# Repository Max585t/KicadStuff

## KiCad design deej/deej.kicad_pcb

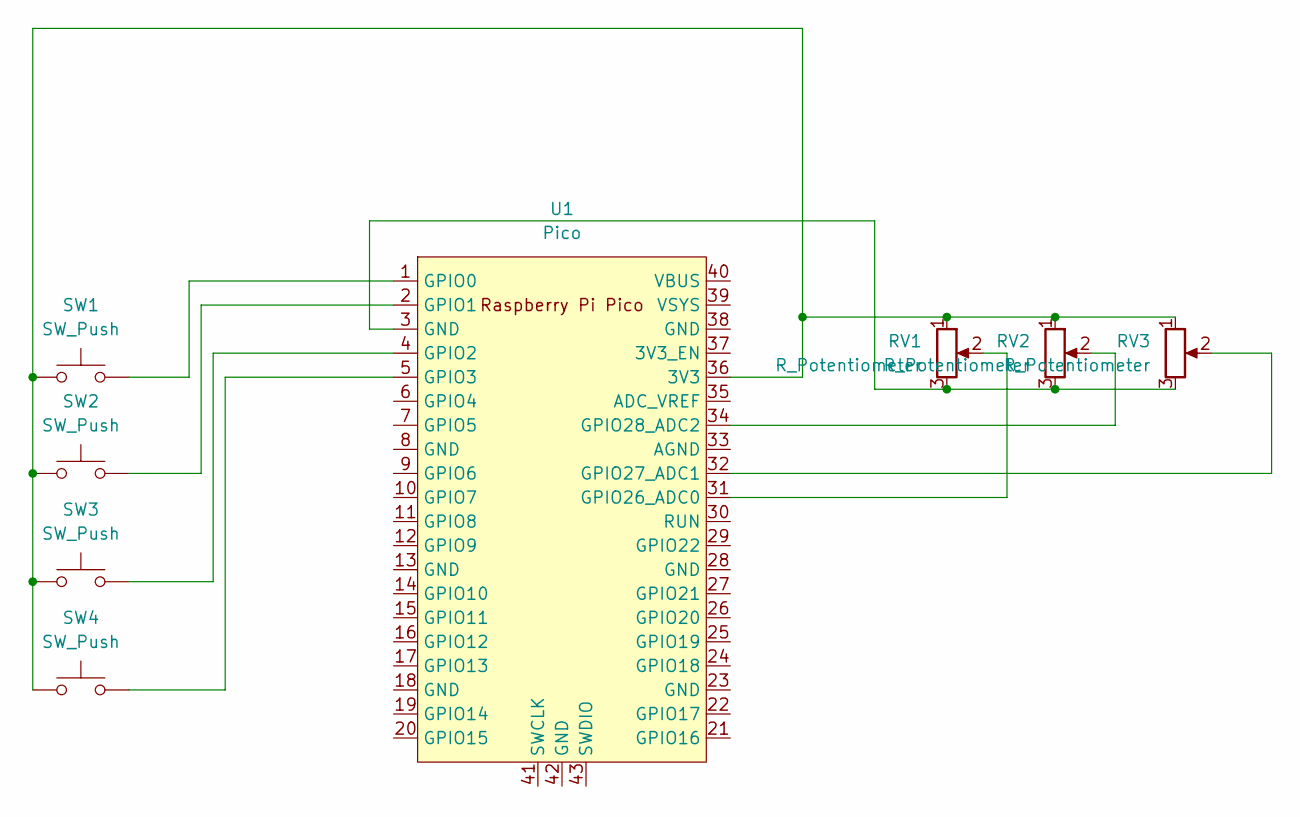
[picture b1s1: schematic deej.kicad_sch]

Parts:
RV1, RV2, RV3: R_Potentiometer; Potentiometer_Bourns_PTA6043_Single_Slide
SW1, SW2, SW3, SW4: SW_Push; SW_PUSH-12mm
U1: Pico; RPi_Pico_SMD_TH

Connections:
unnamed: RV1.1, RV2.1, RV3.1, SW1.1, SW2.1, SW3.1, SW4.1, U1.36 (3V3)
unnamed: RV1.2, U1.31 (GPIO26_ADC0)
unnamed: RV1.3, RV2.3, RV3.3, U1.3 (GND)
unnamed: SW1.2, U1.1 (GPIO0)
unnamed: SW2.2, U1.2 (GPIO1)
unnamed: SW3.2, U1.4 (GPIO2)
unnamed: SW4.2, U1.5 (GPIO3)
unnamed: RV3.2, U1.32 (GPIO27_ADC1)
unnamed: RV2.2, U1.34 (GPIO28_ADC2)

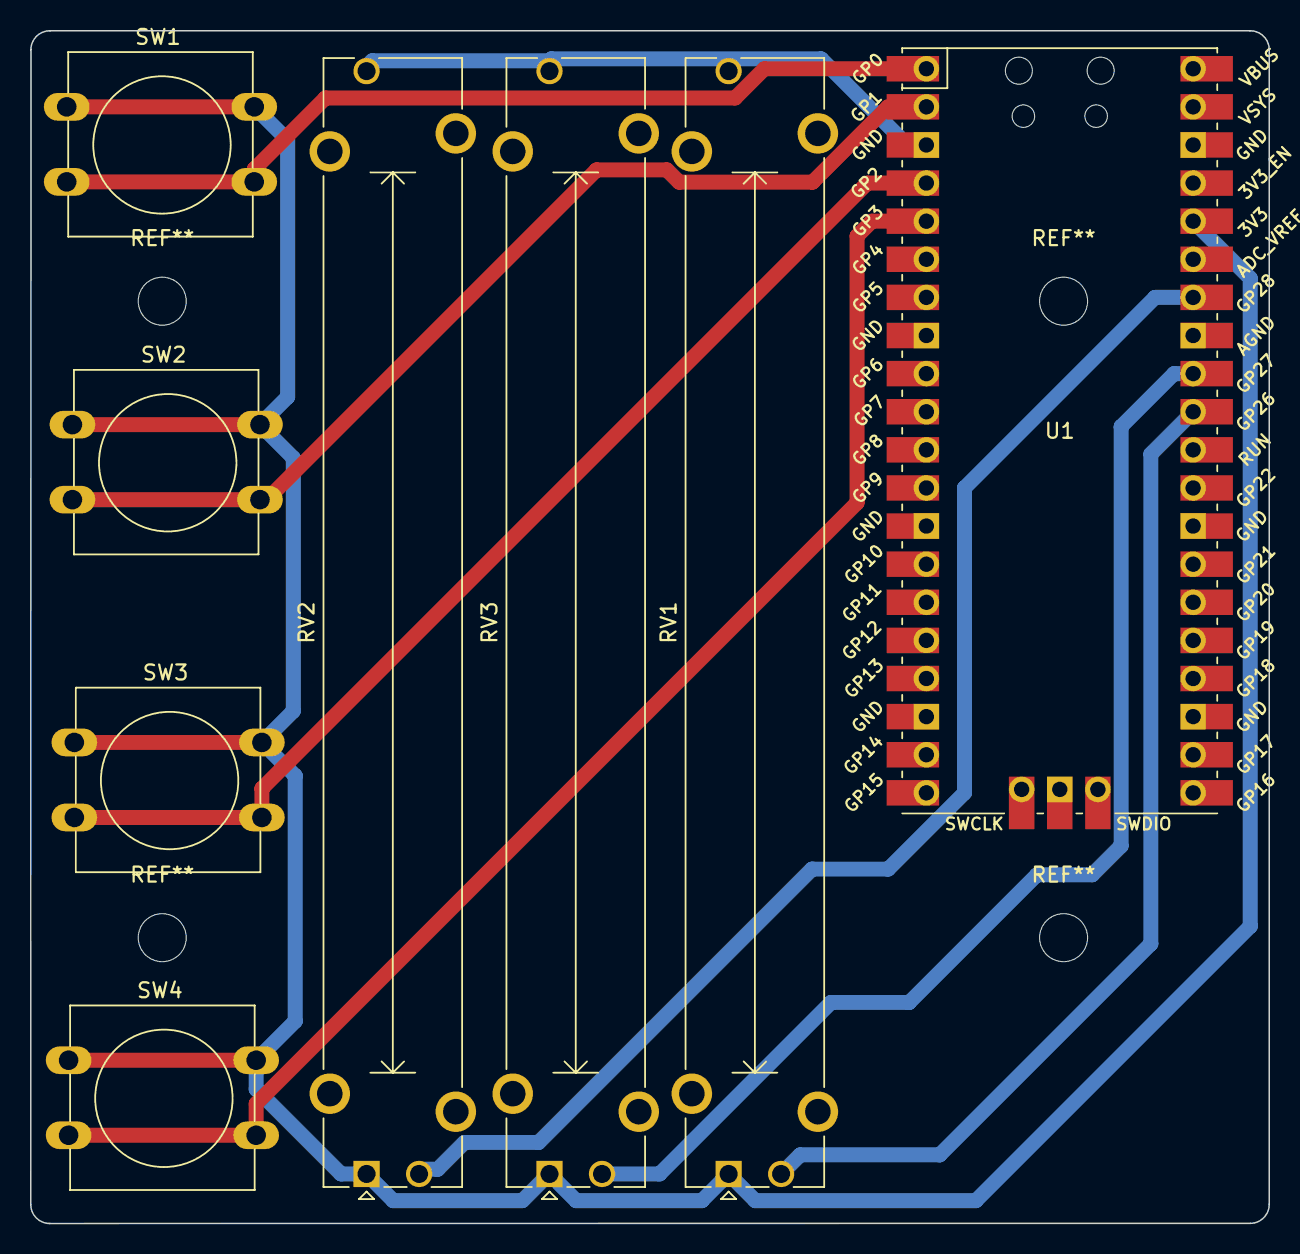
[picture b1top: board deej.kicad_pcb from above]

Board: 2 copper layers, 82.5 x 79.5 mm, 8 parts (0 on the bottom side), 9 nets.
